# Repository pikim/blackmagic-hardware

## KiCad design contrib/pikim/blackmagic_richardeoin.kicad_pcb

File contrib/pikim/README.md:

This version is based on [richardeoins](https://github.com/blacksphere/blackmagic-hardware/tree/master/contrib/richardeoin) hardware variant, but with the following changes:
* 1.27mm connector was replaced by a standard 2.54mm type
* the JTAG pinning was changed according to [mmvisual](https://www.mikrocontroller.net/articles/JTAG#Der_10-polige_JTAG_Stecker_von_mmvisual_.28ARM.2C_Cortex.2C_Seriell_kombiniert.29)
* ported to KiCad
* new board layout
* the board size is 41mm x 17mm

This board has been built and it works.

The filenames are misleading, but were just kept after the conversion from EAGLE.

### Photos

The pictures show the assembled board, which was at that time also an EAGLE design. The design files in this repository were converted and fixed (errors in the solder stop mask) after taking the pictures.

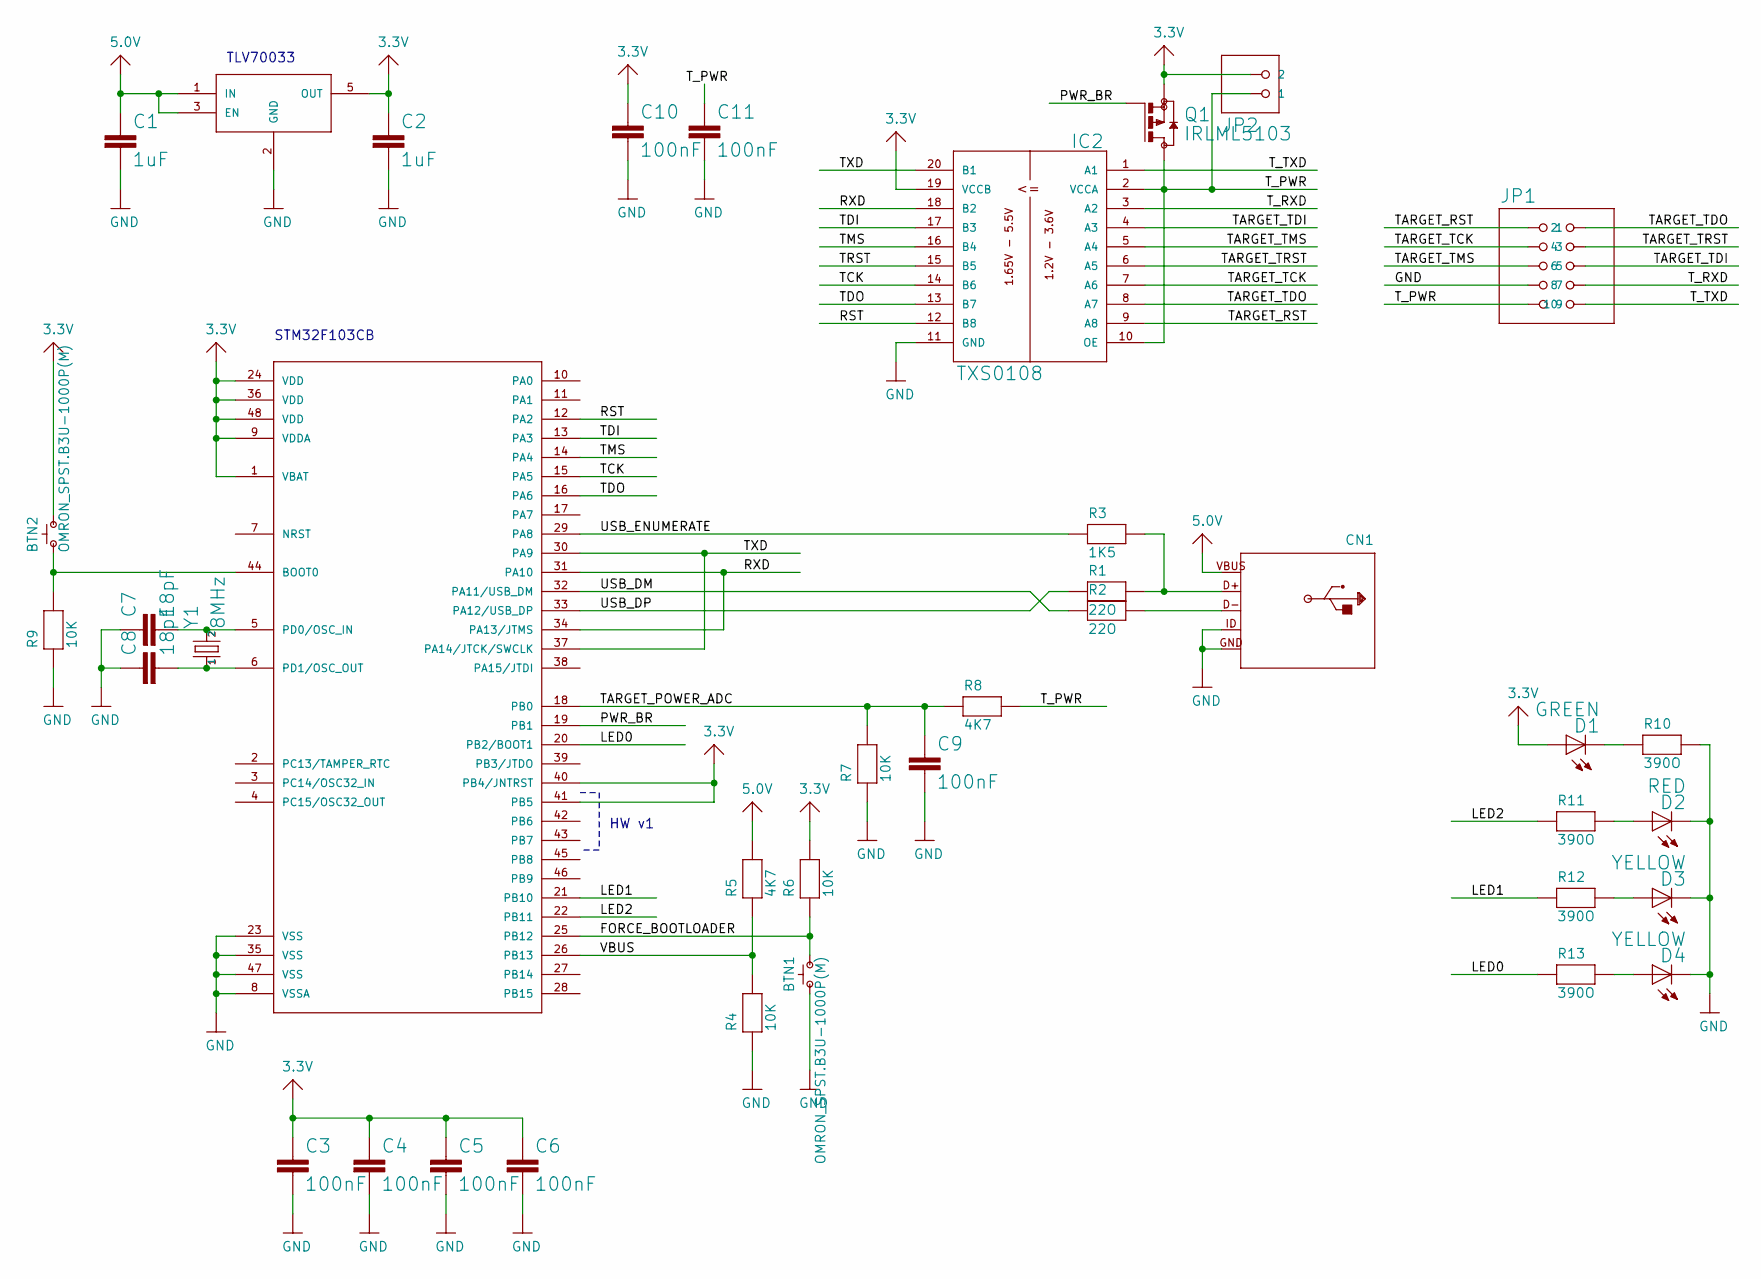
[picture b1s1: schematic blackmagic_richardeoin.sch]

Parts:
BTN1, BTN2: OMRON_SPST.B3U-1000P(M); BLACKMAGIC_RICHARDEOIN_OMRON_B3U-1000P(M)
C1, C2: 1uF; RESISTOR_C0603K
C3, C4, C5, C6, C9, C10, C11: 100nF; RESISTOR_C0603K
C7, C8: 18pF; RESISTOR_C0603K
CN1: MICROBUILDER_V3_USB-MINIB
D1: GREEN; LED_CHIPLED_0603
D2: RED; LED_CHIPLED_0603
D3, D4: YELLOW; LED_CHIPLED_0603
IC1: STM32F_48PIN; STM32F_TQFP48
IC2: TXS0108; DAN-TRANSLATE_TSSOP20
IC3: TLV70033DCK; BLACKMAGIC_RICHARDEOIN_TLV700_SC70-5L
JP1: PINHEAD_2X05
JP2: PINHEAD-2_1X02SMD_90-BIGPADS
Q1: IRLML5103; TRANSISTOR-SMALL-SIGNAL_SOT23
R1, R2: 22O; MICROBUILDER_0603-MINI
R3: 1K5; MICROBUILDER_0603-MINI
R4, R6, R7, R9: 10K; MICROBUILDER_0603-MINI
R5, R8: 4K7; MICROBUILDER_0603-MINI
R10, R11, R12, R13: 390O; MICROBUILDER_0603-MINI
Y1: 8MHz; SPARKFUN_CRYSTAL-SMD-5X3

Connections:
3.3V: BTN2.2, C2.1, C3.1, C4.1, C5.1, C6.1, C10.1, D1.A, IC1.1 (VBAT), IC1.9 (VDDA), IC1.24 (VDD), IC1.36 (VDD), IC1.40 (PB4/JNTRST), IC1.41 (PB5), IC1.48 (VDD), IC2.19 (VCCB), IC3.5 (OUT), JP2.2, Q1.2 (S), R6.2
5.0V: C1.1, CN1.VBUS, IC3.1 (IN), IC3.3 (EN), R5.2
BOOT0: BTN2.1, IC1.44 (BOOT0), R9.2
D+: CN1.D+, R1.2, R3.2
D-: CN1.D-, R2.2
FORCE_BOOTLOADER: BTN1.1, IC1.25 (PB12), R6.1
GND: BTN1.2, C1.2, C2.2, C3.2, C4.2, C5.2, C6.2, C7.1, C8.1, C9.2, C10.2, C11.2, CN1.GND, CN1.GND1, CN1.GND2, CN1.GND3, CN1.GND4, CN1.ID, D2.C, D3.C, D4.C, IC1.8 (VSSA), IC1.23 (VSS), IC1.35 (VSS), IC1.47 (VSS), IC2.11 (GND), IC3.2 (GND), JP1.7, R4.1, R7.1, R9.1, R10.2
LED0: IC1.20 (PB2/BOOT1), R13.1
LED1: IC1.21 (PB10), R12.1
LED2: IC1.22 (PB11), R11.1
LPC_XTAL2: C8.2, IC1.6 (PD1/OSC_OUT), Y1.1
unnamed: D2.A, R11.2
unnamed: D1.C, R10.1
unnamed: D3.A, R12.2
unnamed: D4.A, R13.2
OSC_IN: C7.2, IC1.5 (PD0/OSC_IN), Y1.3 (2)
PWR_BR: IC1.19 (PB1), Q1.1 (G)
RST: IC1.12 (PA2), IC2.12 (B8)
RXD: IC1.31 (PA10), IC1.34 (PA13/JTMS), IC2.18 (B2)
TARGET_POWER_ADC: C9.1, IC1.18 (PB0), R7.2, R8.1
TARGET_RST: IC2.9 (A8), JP1.1
TARGET_TCK: IC2.7 (A6), JP1.3
TARGET_TDI: IC2.4 (A3), JP1.6
TARGET_TDO: IC2.8 (A7), JP1.2
TARGET_TMS: IC2.5 (A4), JP1.5
TARGET_TRST: IC2.6 (A5), JP1.4
TCK: IC1.15 (PA5), IC2.14 (B6)
TDI: IC1.13 (PA3), IC2.17 (B3)
TDO: IC1.16 (PA6), IC2.13 (B7)
TMS: IC1.14 (PA4), IC2.16 (B4)
TRST: IC2.15 (B5)
TXD: IC1.30 (PA9), IC1.37 (PA14/JTCK/SWCLK), IC2.20 (B1)
T_PWR: C11.1, IC2.2 (VCCA), IC2.10 (OE), JP1.9, JP2.1, Q1.3 (D), R8.2
T_RXD: IC2.3 (A2), JP1.8
T_TXD: IC2.1 (A1), JP1.10
USB_DM: IC1.32 (PA11/USB_DM), R2.1
USB_DP: IC1.33 (PA12/USB_DP), R1.1
USB_ENUMERATE: IC1.29 (PA8), R3.1
VBUS: IC1.26 (PB13), R4.2, R5.1

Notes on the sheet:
STM32F103CB
HW v1
TLV70033

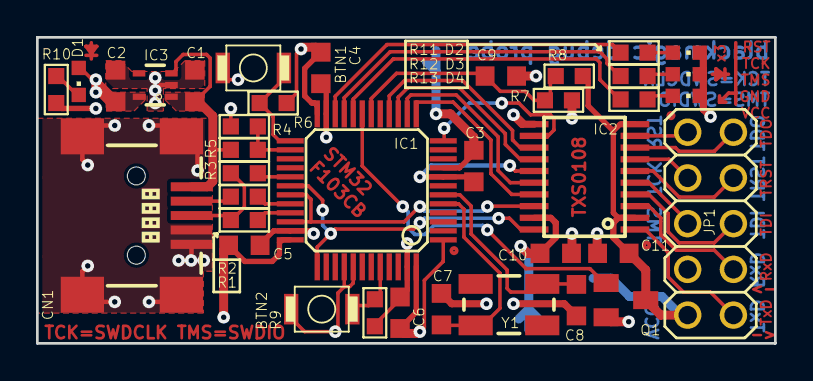
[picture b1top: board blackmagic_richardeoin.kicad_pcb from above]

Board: 2 copper layers, 41.0 x 17.0 mm, 39 parts (0 on the bottom side), 38 nets.

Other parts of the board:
U$32: LP_NUMBER_SILK_TOP

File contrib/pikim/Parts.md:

## Parts List

| ID | Part Number | Description | Supplier | Order Code | Quantity
| --- | --- | --- | --- | --- | ---
| IC1 | STM32F103CBT6 | Microcontroller, 128Kb Flash, 20Kb SRAM, -40 to 85°C | Farnell | [1606327](http://uk.farnell.com/jsp/search/browse.jsp;jsessionid=0?N=0&Ntk=partnumbers&Ntt=*1606327*) | 1
| JP1 |  | 2x5 Pin Header, SMT, 2.54mm Pitch, Gold Plate |  |  | 1
| CN1 | 67503-1230 | USB Mini B Receptacle, SMT | Farnell | [2313554](http://uk.farnell.com/jsp/search/browse.jsp;jsessionid=0?N=0&Ntk=partnumbers&Ntt=*2313554*) | 1
| BTN1, BTN2 | B3U-1000P-B | SPST-NO Switch, SMD | Farnell | [1333654](http://uk.farnell.com/jsp/search/browse.jsp;jsessionid=0?N=0&Ntk=partnumbers&Ntt=*1333654*) | 2
| Q1 | IRLML5103PBF | MOSFET, P, -30V, -0.61A, SOT-23 | Farnell | [8660085](http://uk.farnell.com/jsp/search/browse.jsp;jsessionid=0?N=0&Ntk=partnumbers&Ntt=*8660085*) | 1
| IC2 | TXS0108EPWR | Bidirectional Voltage Translator, 8-bit, 20TSSOP | Farnell | [1702548](http://uk.farnell.com/jsp/search/browse.jsp;jsessionid=0?N=0&Ntk=partnumbers&Ntt=*1702548*) | 1
| IC3 | TLV70033DCKT | LDO Regulator, 3.3V 200mA, 5SC70 | Farnell | [1815750](http://uk.farnell.com/jsp/search/browse.jsp;jsessionid=0?N=0&Ntk=partnumbers&Ntt=*1815750*) | 1
| Y1 | ABMM2-8.000MHZ-E2-T | Crystal, 8MHz, 18pF, 6x3.6mm | Farnell | [1611803](http://uk.farnell.com/jsp/search/browse.jsp;jsessionid=0?N=0&Ntk=partnumbers&Ntt=*1611803*) | 1
| R1, R2 | MC0063W0603122R | Resistor 22Ω, 0.063W, 1%, 0603 [1608 Metric] | Farnell | [9330844](http://uk.farnell.com/jsp/search/browse.jsp;jsessionid=0?N=0&Ntk=partnumbers&Ntt=*9330844*) | 2
| R3 | MC0063W060311K5 | Resistor 1.5KΩ, 0.063W, 1%, 0603 [1608 Metric] | Farnell | [9330607](http://uk.farnell.com/jsp/search/browse.jsp;jsessionid=0?N=0&Ntk=partnumbers&Ntt=*9330607*) | 1
| R4, R6, R7, R9 | MC0063W0603110K | Resistor 10KΩ, 0.063W, 1%, 0603 [1608 Metric] | Farnell | [9330399](http://uk.farnell.com/jsp/search/browse.jsp;jsessionid=0?N=0&Ntk=partnumbers&Ntt=*9330399*) | 4
| R5, R8 | MC0063W060314K7 | Resistor 4.7KΩ, 0.063W, 1%, 0603 [1608 Metric] | Farnell | [9331247](http://uk.farnell.com/jsp/search/browse.jsp;jsessionid=0?N=0&Ntk=partnumbers&Ntt=*9331247*) | 2
| R10, R11, R12, R13 | MC0063W06031390R | Resistor 390Ω, 0.063W, 1%, 0603 [1608 Metric] | Farnell | [9331131](http://uk.farnell.com/jsp/search/browse.jsp;jsessionid=0?N=0&Ntk=partnumbers&Ntt=*9331131*) | 4
| D1 | KPT-1608SGC | LED, Green 568nm, 0603 [1608 Metric] | Farnell | [2099223](http://uk.farnell.com/jsp/search/browse.jsp;jsessionid=0?N=0&Ntk=partnumbers&Ntt=*2099223*) | 1
| D2 | KPT-1608EC | LED, Red 625nm, 0603 [1608 Metric] | Farnell | [2099221](http://uk.farnell.com/jsp/search/browse.jsp;jsessionid=0?N=0&Ntk=partnumbers&Ntt=*2099221*) | 1
| D3, D4 | KPT-1608YC | LED, Yellow 588nm, 0603 [1608 Metric] | Farnell | [2099227](http://uk.farnell.com/jsp/search/browse.jsp;jsessionid=0?N=0&Ntk=partnumbers&Ntt=*2099227*) | 2
| C1, C2 | MC0603X105K100CT | Capacitor 1µF, X5R, 10V, 0603 [1608 Metric] | Farnell | [1759399](http://uk.farnell.com/jsp/search/browse.jsp;jsessionid=0?N=0&Ntk=partnumbers&Ntt=*1759399*) | 2
| C3, C4, C5, C6, C9, C10, C11 | MC0603B104K500CT | Capacitor 100nF, X7R, 50V, 0603 [1608 Metric] | Farnell | [1759122](http://uk.farnell.com/jsp/search/browse.jsp;jsessionid=0?N=0&Ntk=partnumbers&Ntt=*1759122*) | 7
| C7, C8 | MC0603N180J500CT | Capacitor 18pF, C0G / NP0, 50V, 0603 [1608 Metric] | Farnell | [1759056](http://uk.farnell.com/jsp/search/browse.jsp;jsessionid=0?N=0&Ntk=partnumbers&Ntt=*1759056*) | 2

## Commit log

2017-02-18 Added new board variant based on richardeoins
